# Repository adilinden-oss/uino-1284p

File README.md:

## \*uino-1284p 

\*uino-1284p is an Arduino compatible platform based on the Atmel ATmega1284P-AU microcontroller.

### Licensing

This work is licensed under a Creative Commons Attribution-ShareAlike 3.0 Unported License, CC BY-SA.

You are free to copy, distribute and transmit the work. You must attribute the work in the manner specified by the author or licensor (but not in any way that suggests that they endorse you or your use of the work). you alter, transform, or build upon this work, you may distribute the resulting work only under the same or similar license to this one.  

Please refer to [http://creativecommons.org/licenses/by-sa/3.0/] for the license.

### Credit

The \*uino-1284p is derived from previous work done by:

- The Arduino team <http://arduino.cc/>

### Details

The \*uino-1284p board utilizes the ATmega1284P microcontroller. The main goal of this project is to be able to access more memory, both FLASH and RAM, while keeping the Arduino UNO compatible board size and I/O assignments.

The ATmega1284P provides 128k of FLASH and 16k of RAM. It has 10 more I/O pins then the ATmega328P. The additional I/O pins are brought out to a 5x2 header in a non-standard Arduino position. The extra header pins are :

        L1/D16  o|o  L2/D17
           D18  o|o  D19
           D20  o|o  D21
           D22  o|o  D23
        D24/A6  o|o  D25/A7

The design features a dedicated ATmega8U2 for USB connectivity. The circuit has been taken from the Arduino UNO but the TQFP-32 package was chosen for easy solderability.

Power supply input for the board is selected via a jumper. Power supply options are USB bus powered or unregulated DC input. An onboard LDO regulator will accept an unregulated input voltage between 6.4V and 15V.

### Arduino

The board is supported in Arduino IDE 1.6.x via the core files available at: [adilinden-oss/uino-arduino](https://github.com/adilinden-oss/uino-arduino)

To install clone uino-arduino into the hardware folder inside your Sketchbook folder. The board will then automagically appear in the Boards menu.

### Pin Mapping

```
*uino     ATmega1284p                     Function
A0  D26   32 - PA5 (PCINT5/ADC5)
A1  D27   33 - PA4 (PCINT4/ADC4)
A2  D28   34 - PA3 (PCINT3/ADC3)
A3  D29   35 - PA2 (PCINT2/ADC2)
A4  D30   36 - PA1 (PCINT1/ADC1)
A5  D31   37 - PA0 (PCINT0/ADC0)

D0        9  - PD0 (PCINT24/RXD0/T3)      UART RX0
D1        10 - PD1 (PCINT25/TXD0)         UART TX0
D2        11 - PD2 (PCINT26/RXD1/INT0)    IRQ2, UART RX1
D3        12 - PD3 (PCINT27/TXD1/INT1)    IRQ3, UART TX1
D4        13 - PD4 (PCINT28/XCK1/OC1B)    PWM
D5        14 - PD5 (PCINT29/OC1A)         PWM
D6        15 - PD6 (PCINT30/OC2B/ICP)     PWM
D7        16 - PD7 (PCINT31/OC2A)         PWM

D8        42 - PB2 (PCINT10/INT2/AIN0)  
D9        43 - PB3 (PCINT11/OC0A/AIN1)    PWM
D10       44 - PB4 (PCINT12/OC0B/SS)      PWM, SPI SS
D11       1  - PB5 (PCINT13/ICP3/MOSI)    SPI MOSI
D12       2  - PB6 (PCINT14/OC3A/MISO)    PWM, SPI MISO
D13       3  - PB7 (PCINT15/OC3B/SCK)     PWM, SPI SCK, LED

SCL D14   19 - PC0 (PCINT16/SCL)          SCL
SDA D15   20 - PC1 (PCINT17/SDA)          SDA
L1  D16   21 - PC2 (PCINT18/TCK)          L1
L2  D17   22 - PC3 (PCINT19/TMS)          L2

D18       23 - PC4 (PCINT20/TDO)
D19       24 - PC5 (PCINT21/TDI)
D20       25 - PC6 (PCINT22/TOSC1)
D21       26 - PC7 (PCINT23/TOSC2)
D22       40 - PB0 (PCINT8/T0/XCK0)
D23       41 - PB1 (PCINT9/T1/CLK0)
A6  D24   30 - PA7 (PCINT7/ADC7)
A7  D25   31 - PA6 (PCINT6/ADC6)
```

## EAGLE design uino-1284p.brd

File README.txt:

*uino-1284p is an Arduino compatible platform based on the ATmega1284P-AU

Licensing
---------
This work is licensed under a Creative Commons Attribution-ShareAlike 3.0 
Unported License, CC BY-SA.

You are free to copy, distribute and transmit the work. You must attribute 
the work in the manner specified by the author or licensor (but not in any
way that suggests that they endorse you or your use of the work). you alter,
transform, or build upon this work, you may distribute the resulting work
only under the same or similar license to this one.  

Please refer to <http://creativecommons.org/licenses/by-sa/3.0/> for the
license.

Credit
------
The *uino-1284p is derived from previous work done by:
- The Arduino team <http://arduino.cc/>

Details
-------
The *uino-1284p board utilizes the ATmega1284P microcontroller. The main goal of
this project is to be able to access more memory, both FLASH and RAM, while
keeping the Arduino UNO compatible board size and I/O assignments.

The ATmega1284P provides 128k of FLASH and 16k of RAM. It has 10 more I/O pins
then the ATmega328P. The additional I/O pins are brought out to a 5x2 header
in a non-standard Arduino position.

The design features a dedicated ATmega8U2 for USB connectivity. The circuit
has been taken from the Arduino UNO but the TQFP-32 package was chosen for easy
solderability.

Power supply input for the board is selected via a jumper. Power supply options
are USB bus powered or unregulated DC input. An onboard LDO regulator will accept
an unregulated input voltage between 6.4V and 15V.

Arduino
-------
The board is supported in Arduino IDE 1.6.x via the core files available at:
https://github.com/adilinden/uino-arduino

To install clone uino-arduino into the hardware folder inside your Sketchbook
folder. The board will then automagically appear in the Boards menu.

Pin Mapping
-----------

Note that the pin mappings do not quite match the schematic diagram.  Header
J6 which is the 5x2 header provided for additional I/O has been renumbered.
The schematic diagram will have to be updated some time.  Since these are not
labelled on the board there are no other visible changes.

The new header pins are now:

		L1/D16  o|o  L2/D17
		   D18  o|o  D19
		   D20  o|o  D21
		   D22  o|o  D23
		D24/A6  o|o  D25/A7

*uino     ATmega1284p                     Function
A0  D26   32 - PA5 (PCINT5/ADC5)
A1  D27   33 - PA4 (PCINT4/ADC4)
A2  D28   34 - PA3 (PCINT3/ADC3)
A3  D29   35 - PA2 (PCINT2/ADC2)
A4  D30   36 - PA1 (PCINT1/ADC1)
A5  D31   37 - PA0 (PCINT0/ADC0)

D0        9  - PD0 (PCINT24/RXD0/T3)      UART RX0
D1        10 - PD1 (PCINT25/TXD0)         UART TX0
D2        11 - PD2 (PCINT26/RXD1/INT0)    IRQ2, UART RX1
D3        12 - PD3 (PCINT27/TXD1/INT1)    IRQ3, UART TX1
D4        13 - PD4 (PCINT28/XCK1/OC1B)    PWM
D5        14 - PD5 (PCINT29/OC1A)         PWM
D6        15 - PD6 (PCINT30/OC2B/ICP)     PWM
D7        16 - PD7 (PCINT31/OC2A)         PWM

D8        42 - PB2 (PCINT10/INT2/AIN0)  
D9        43 - PB3 (PCINT11/OC0A/AIN1)    PWM
D10       44 - PB4 (PCINT12/OC0B/SS)      PWM, SPI SS
D11       1  - PB5 (PCINT13/ICP3/MOSI)    SPI MOSI
D12       2  - PB6 (PCINT14/OC3A/MISO)    PWM, SPI MISO
D13       3  - PB7 (PCINT15/OC3B/SCK)     PWM, SPI SCK, LED

SCL D14   19 - PC0 (PCINT16/SCL)          SCL
SDA D15   20 - PC1 (PCINT17/SDA)          SDA
L1  D16   21 - PC2 (PCINT18/TCK)          L1
L2  D17   22 - PC3 (PCINT19/TMS)          L2

D18       23 - PC4 (PCINT20/TDO)
D19       24 - PC5 (PCINT21/TDI)
D20       25 - PC6 (PCINT22/TOSC1)
D21       26 - PC7 (PCINT23/TOSC2)
D22       40 - PB0 (PCINT8/T0/XCK0)
D23       41 - PB1 (PCINT9/T1/CLK0)
D24  A6   30 - PA7 (PCINT7/ADC7)
D25  A7   31 - PA6 (PCINT6/ADC6)

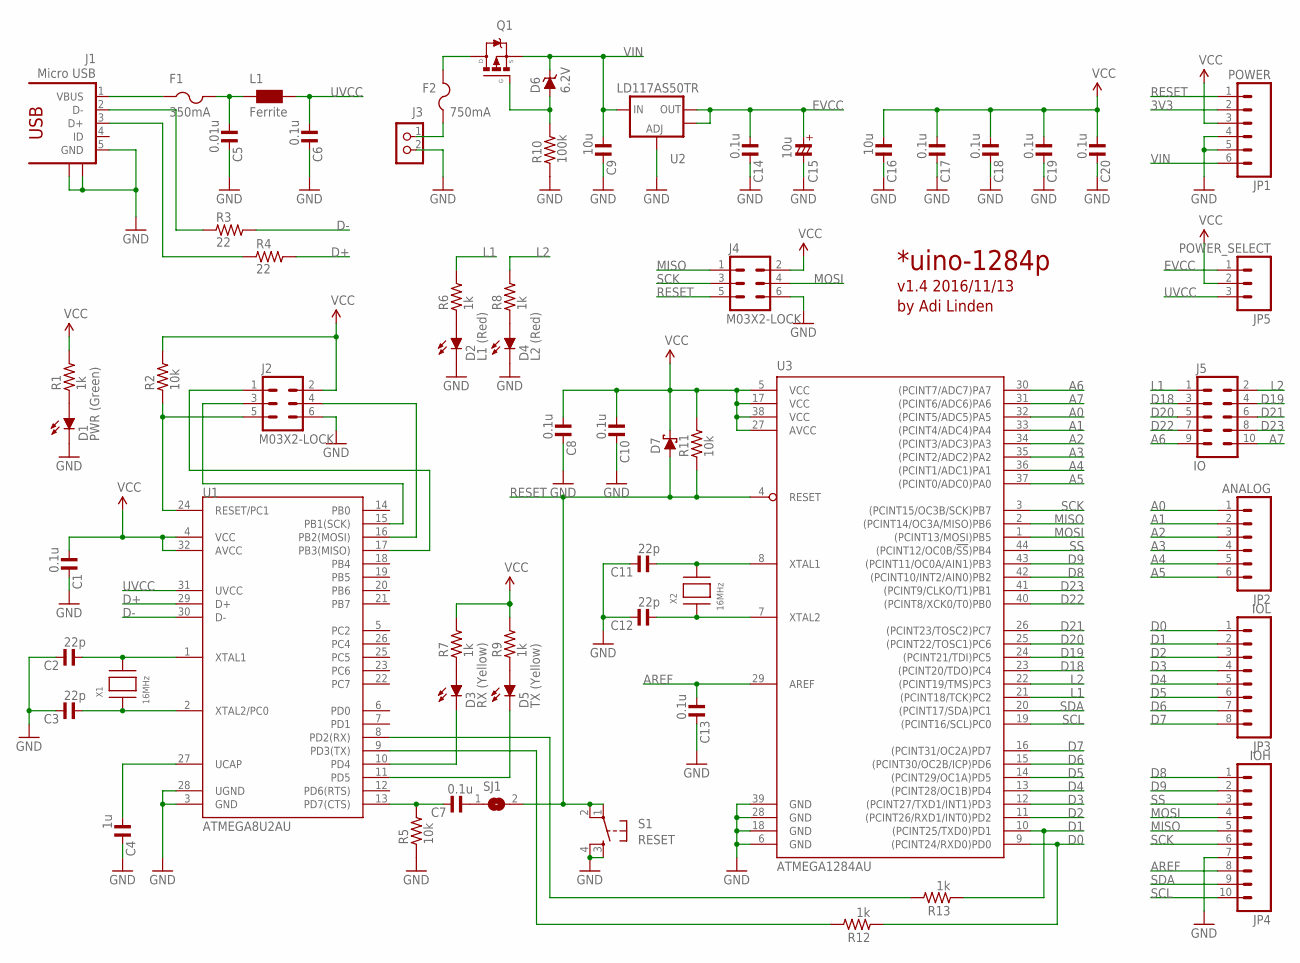
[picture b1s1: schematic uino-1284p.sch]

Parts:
C1, C6, C7, C8, C10, C13, C14, C17, C18, C19, C20: 0.1u; C0805MP
C2, C3, C11, C12: 22p; C0805MP
C4: 1u; C0805MP
C5: 0.01u; C0805MP
C9, C16: 10u; C0805MP
C15: 10u; C0805MP/T
D1: PWR (Green); CHIP-LED0805MP
D2: L1 (Red); CHIP-LED0805MP
D3: RX (Yellow); CHIP-LED0805MP
D4: L2 (Red); CHIP-LED0805MP
D5: TX (Yellow); CHIP-LED0805MP
D6: 6.2V; SOD323
D7: SCHOTTKY-DIODESOD323; SOD323
F1: 350mA; R0805
F2: 750mA; R0805
J1: Micro USB; ZX62D-AB-5P8
J2, J4: M03X2-LOCK; 2X03_LOCK
J3: CON_TERMINAL_BLOCK_02-5MM; TERMINAL_BLOCK_2P_5
J5: IO; 2X05
JP1: POWER; 1X06
JP2: ANALOG; 1X06
JP3: IOL; 1X08
JP4: IOH; 1X10
JP5: POWER_SELECT; 1X03
L1: Ferrite; 0805
Q1: MMBF0202PLT1; SOT23
R1, R6, R7, R8, R9, R12, R13: 1k; R0805MP
R2, R5, R11: 10k; R0805MP
R3, R4: 22; R0805MP
R10: 100k; R0805MP
S1: RESET; TACTILE_SWITCH_SMD
SJ1: SJ
U1: ATMEGA8U2AU; TQFP32-08
U2: LD117AS50TR; SOT223
U3: ATMEGA1284AU; TQFP44
X1, X2: 16MHz; NX5032

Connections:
3V3: JP1.2
A0: JP2.1, U3.32 ((PCINT5/ADC5)PA5)
A1: JP2.2, U3.33 ((PCINT4/ADC4)PA4)
A2: JP2.3, U3.34 ((PCINT3/ADC3)PA3)
A3: JP2.4, U3.35 ((PCINT2/ADC2)PA2)
A4: JP2.5, U3.36 ((PCINT1/ADC1)PA1)
A5: JP2.6, U3.37 ((PCINT0/ADC0)PA0)
A6: J5.9, U3.30 ((PCINT7/ADC7)PA7)
A7: J5.10, U3.31 ((PCINT6/ADC6)PA6)
AREF: C13.1, JP4.8, U3.29 (AREF)
D0: JP3.1, R12.1, U3.9 ((PCINT24/RXD0)PD0)
D1: JP3.2, R13.1, U3.10 ((PCINT25/TXD0)PD1)
D2: JP3.3, U3.11 ((PCINT26/RXD1/INT0)PD2)
D3: JP3.4, U3.12 ((PCINT27/TXD1/INT1)PD3)
D4: JP3.5, U3.13 ((PCINT28/OC1B)PD4)
D5: JP3.6, U3.14 ((PCINT29/OC1A)PD5)
D6: JP3.7, U3.15 ((PCINT30/OC2B/ICP)PD6)
D7: JP3.8, U3.16 ((PCINT31/OC2A)PD7)
D8: JP4.1, U3.42 ((PCINT10/INT2/AIN0)PB2)
D9: JP4.2, U3.43 ((PCINT11/OC0A/AIN1)PB3)
D18: J5.3, U3.23 ((PCINT20/TDO)PC4)
D19: J5.4, U3.24 ((PCINT21/TDI)PC5)
D20: J5.5, U3.25 ((PCINT22/TOSC1)PC6)
D21: J5.6, U3.26 ((PCINT23/TOSC2)PC7)
D22: J5.7, U3.40 ((PCINT8/XCK0/T0)PB0)
D23: J5.8, U3.41 ((PCINT9/CLKO/T1)PB1)
D+: R4.2, U1.29 (D+)
D-: R3.2, U1.30 (D-)
EVCC: C14.1, C15.+, JP5.1, U2.2 (OUT), U2.4 (OUT)
GND: C1.2, C2.2, C3.2, C4.2, C5.2, C6.2, C8.2, C9.2, C10.2, C11.2, C12.2, C13.2, C14.2, C15.-, C16.2, C17.2, C18.2, C19.2, C20.2, D1.C, D2.C, D4.C, J1.5 (GND), J1.S1, J1.S2, J2.6, J3.2, J4.6, JP1.4, JP1.5, JP4.7, R5.1, R10.1, S1.3, S1.4, U1.3 (GND), U1.28 (UGND), U2.1 (ADJ), U3.6 (GND), U3.18 (GND), U3.28 (GND), U3.39 (GND)
L1: J5.1, R6.2, U3.21 ((PCINT18/TCK)PC2)
L2: J5.2, R8.2, U3.22 ((PCINT19/TMS)PC3)
MISO: J4.1, JP4.5, U3.2 ((PCINT14/OC3A/MISO)PB6)
MOSI: J4.4, JP4.4, U3.1 ((PCINT13/MOSI)PB5)
unnamed: F2.2, Q1.3 (D)
unnamed: C5.1, F1.2, L1.1
unnamed: C7.1, SJ1.1
unnamed: J1.2 (D-), R3.1
unnamed: J1.3 (D+), R4.1
unnamed: R12.2, U1.9 (PD3(TX))
unnamed: R13.2, U1.8 (PD2(RX))
unnamed: C2.1, U1.1 (XTAL1), X1.P$2
unnamed: C3.1, U1.2 (XTAL2/PC0), X1.P$1
unnamed: C4.1, U1.27 (UCAP)
unnamed: D2.A, R6.1
unnamed: D4.A, R8.1
unnamed: J2.1, U1.17 (PB3(MISO))
unnamed: J2.3, U1.15 (PB1(SCK))
unnamed: J2.5, R2.1, U1.24 (RESET/PC1)
unnamed: J2.4, U1.16 (PB2(MOSI))
unnamed: F2.1, J3.1
unnamed: D6.A, Q1.1 (G), R10.2
unnamed: C11.1, U3.8 (XTAL1), X2.P$2
unnamed: C12.1, U3.7 (XTAL2), X2.P$1
unnamed: D3.A, R7.1
unnamed: D5.A, R9.1
unnamed: D3.C, U1.10 (PD4)
unnamed: D5.C, U1.11 (PD5)
unnamed: C7.2, R5.2, U1.13 (PD7(CTS))
unnamed: D1.A, R1.1
RESET: D7.A, J4.5, JP1.1, R11.1, S1.1, S1.2, SJ1.2, U3.4 (RESET)
SCK: J4.3, JP4.6, U3.3 ((PCINT15/OC3B/SCK)PB7)
SCL: JP4.10, U3.19 ((PCINT16/SCL)PC0)
SDA: JP4.9, U3.20 ((PCINT17/SDA)PC1)
SS: JP4.3, U3.44 ((PCINT12/OC0B/!SS!)PB4)
UVCC: C6.1, JP5.3, L1.2, U1.31 (UVCC)
VBUS: F1.1, J1.1 (VBUS)
VCC: C1.1, C8.1, C10.1, C16.1, C17.1, C18.1, C19.1, C20.1, D7.C, J2.2, J4.2, JP1.3, JP5.2, R1.2, R2.2, R7.2, R9.2, R11.2, U1.4 (VCC), U1.32 (AVCC), U3.5 (VCC), U3.17 (VCC), U3.27 (AVCC), U3.38 (VCC)
VIN: C9.1, D6.C, JP1.6, Q1.2 (S), U2.3 (IN)

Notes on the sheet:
*uino-1284p
v1.4 2016/11/13
by Adi Linden

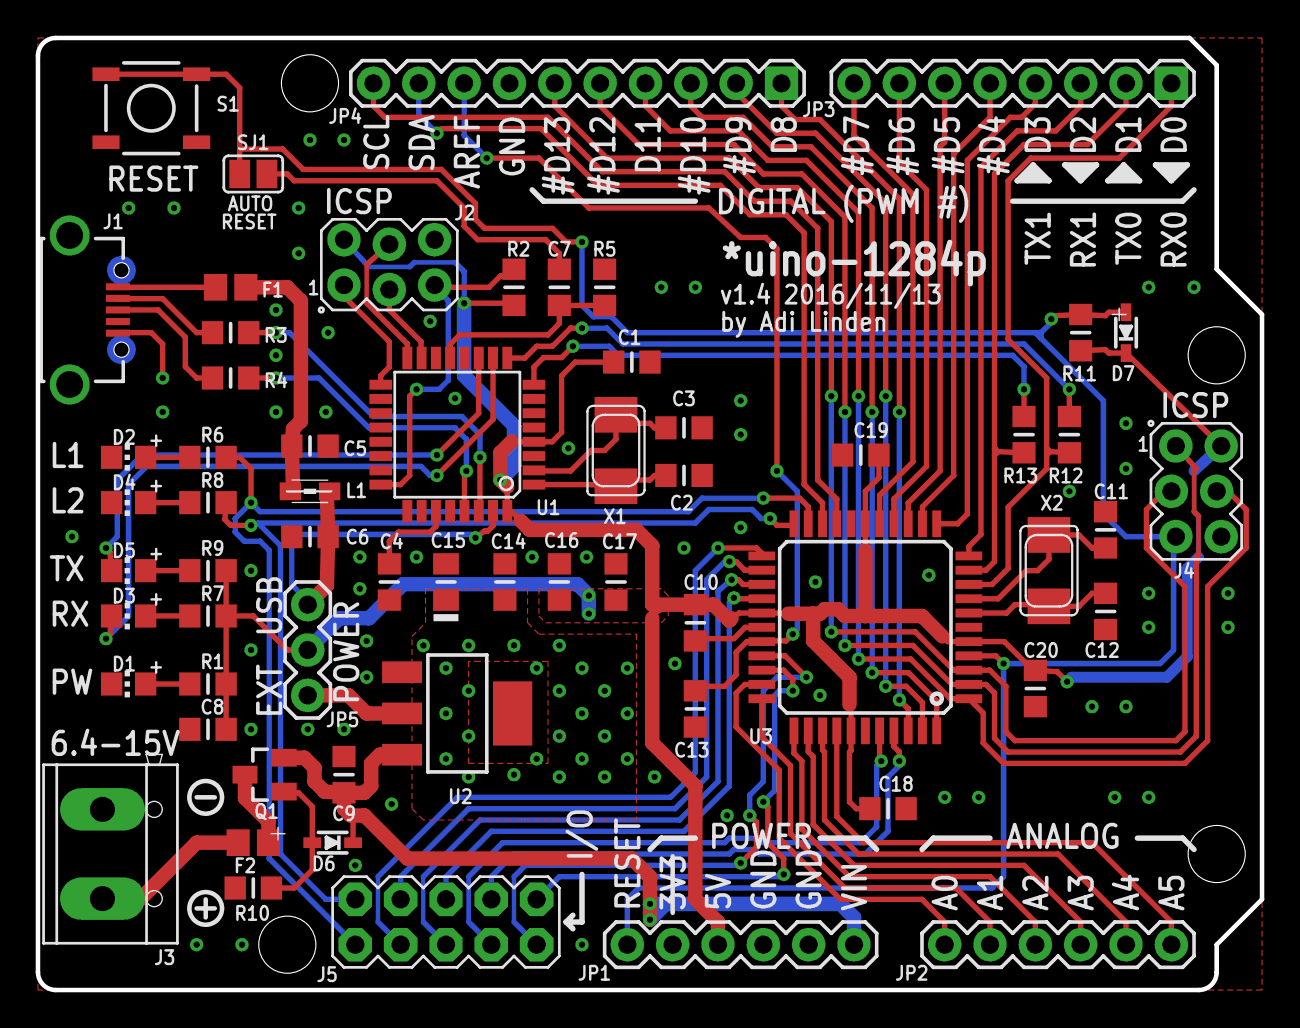
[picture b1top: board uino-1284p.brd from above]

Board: 2 copper layers, 68.6 x 53.3 mm, 61 parts (0 on the bottom side), 68 nets.

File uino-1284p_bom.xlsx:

Part | Quantity | Value | Manufacturer Part Number | DigiKey Part Number | Package | Description
C1, C6, C7, C8, C10, C13, C14, C17, C18, C19, C20 | 11 | 0.1u | CL21B104KBFNNNG | 1276-6468-1-ND | C0805 | 0.10µF ±10% 50V Ceramic Capacitor X7R 0805 (2012 Metric)
C2, C3, C11, C12 | 4 | 22p | CL21C220JBANNNC | 1276-1047-1-ND | C0805 | 22pF ±5% 50V Ceramic Capacitor C0G, NP0 0805 (2012 Metric)
C4 | 1 | 1u | CL21B105KOFNNNG | 1276-6471-1-ND | C0805 | 1µF ±10% 16V Ceramic Capacitor X7R 0805 (2012 Metric)
C5 | 1 | 0.01u | CL21B103KBANNNC | 1276-1015-1-ND | C0805 | 10000pF ±10% 50V Ceramic Capacitor X7R 0805 (2012 Metric)
C9, C16 | 2 | 10u | CL21A106KOQNNNG | 1276-6455-1-ND | C0805 | 10µF ±10% 16V Ceramic Capacitor X5R 0805 (2012 Metric)
C15 | 1 | 10u | F920J106MPA | 478-8115-1-ND | C0805 | 10µF ±20% Molded Tantalum Capacitors 6.3V 0805 (2012 Metric) 6 Ohm
D1 | 1 | 6.2V Zener | DZ2J062M0L | DZ2J062M0LCT-ND | SOD323 | Zener Diode 6.2V 200mW ±5% Surface Mount SMini2-F5-B
D2 | 1 | 1A Schottky | DB2J31700LCT-ND | DB2J31700L | SOD323 | Diode Schottky 30V 1A Surface Mount SMini2-F5-B
F1 | 1 | 350mA | 0ZCK0035FF2G | 507-1812-1-ND | R0805 | PTC Resettable Fuse 6V 350mA Ih Surface Mount 0805 (2012 Metric), Concave
F2 | 1 | 750mA | 0ZCK0075FF2E | 507-1814-1-ND | R0805 | PTC Resettable Fuse 6V 750mA Ih Surface Mount 0805 (2012 Metric), Concave
J1 | 1 | Micro USB | 475890001 | WM17143CT-ND | ZX62D-AB-5P8 | USB - micro AB Receptacle Connector 5 Position Surface Mount, Right Angle, Hori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
J2, J4 | 2 | Header 2x3 | M20-9980345 | 952-2120-ND | 2X03 | 6 Positions Header, Unshrouded, Breakaway Connector 0.100" (2.54mm) Through Hol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
J3 | 1 | Terminal | OSTTC022162 | ED2609-ND | 7.6x10.16mm | 2 Position Wire to Board Terminal Block Horizontal with Board 0.200" (5.08mm) T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
J5 | 1 | Header 2x5 | PPTC052LFBN-RC | S6105-ND | 2X05 | 10 Position Header Connector 0.100" (2.54mm) Through Hole Tin
JP1, JP2 | 2 | Header 1x6 | PPTC061LFBN-RC | S7004-ND | 1X06 | 6 Position Header Connector 0.100" (2.54mm) Through Hole Tin
JP3 | 1 | Header 1x8 | PPTC081LFBN-RC | S7006-ND | 1X08 | 8 Position Header Connector 0.100" (2.54mm) Through Hole Tin
JP4 | 1 | Header 1x10 | PPTC101LFBN-RC | S7008-ND | 1X10 | 10 Position Header Connector 0.100" (2.54mm) Through Hole Tin
JP5 | 1 | Header 1x3 | M20-9990345 | 952-2263-ND | 1X03 | Header 3
L1 | 1 | Ferrite | MI0805K400R-10 | 240-2389-1-ND | L0805 | FERRITE BEAD 40 OHM 0805 1LN
LED1 | 1 | PWR (Green) | LTST-S220KGKT | 160-1468-1-ND | CHIP-LED0805 | Green 568nm LED Indication - Discrete 2V 0805 (2012 Metric)
LED2, LED4 | 2 | L1 (Red) | LTST-S220KRKT | 160-1469-1-ND | CHIP-LED0805 | Red 631nm LED Indication - Discrete 2V 0805 (2012 Metric)
LED3, LED5 | 2 | RX (Yellow) | LTST-S220KSKT | 160-1470-1-ND | CHIP-LED0805 | Yellow 589nm LED Indication - Discrete 2V 0805 (2012 Metric)
Q1 | 1 | P-FET | IRLML2244TRPBF | IRLML2244TRPBFCT-ND | SOT23 | MOSFET P-CH 20V 4.3A SOT23
R1, R6, R7, R8, R9, R12, R13 | 7 | 1k | RC0805JR-071KL | 311-1.0KARCT-ND | R0805 | RES SMD 1K OHM 5% 1/8W 0805
R2, R5, R11 | 3 | 10k | RC0805JR-0710KL | 311-10KARCT-ND | R0805 | RES SMD 10K OHM 5% 1/8W 0805
R3, R4 | 2 | 22 | RC0805JR-0722RL | 311-22ARCT-ND | R0805 | RES SMD 22 OHM 5% 1/8W 0805
R10 | 1 | 100k | RC0805JR-07100KL | 311-100KARCT-ND | R0805 | RES SMD 100K OHM 5% 1/8W 0805
S1 | 1 | RESET | TL3305AF160QG | EG5350CT-ND | 4.50x4.50mm | Tactile Switch SPST-NO Top Actuated Surface Mount
U1 | 1 | ATMEGA8U2AU | ATMEGA8U2-AUR | ATMEGA8U2-AURCT-ND | TQFP32-08 | Atmel 8-bit Microcontroller with 8/16/32K Bystes of ISP Flash and USB Controlle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
U2 | 1 | LD1117S50 | AZ1117IH-5.0TRG1 | AZ1117IH-5.0TRG1DICT-ND | SOT223 | Voltage Regulator LM1117
U3 | 1 | ATMEGA1284AU | ATMEGA1284P-AUR | ATMEGA1284P-AURCT-ND | TQFP44 | 8-bit Microcontroller with 64K Bytes In-System Programmable Flash
X1, X2 | 2 | 16MHz | NX5032GA-16.000000MHZ-LN-CD-1 | 644-1037-1-ND | NX5032 | Low cost SMT crystals, no capacitors included

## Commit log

2011-12-29 Added .gitignore to prevent Eagle backup files from being tracked.
2011-12-30 Completed the board layout. Completed silk screen.
2011-12-30 Added several files.
    Added board, schematic and Gerber files for v0.2.
    Added PNG for v0.2.
2011-12-31 Updated to v0.3.
    - Added 5x2 header to make additional I/O available.
    - Replaced shottky diode on USB supply with jumper for input
    supply voltage selection.
2011-12-31 Added pin assignment for v0.3
2011-12-31 Fixed tabs
2011-12-31 More tab fixes
2016-03-03 Files submitted to Seeed FusionPCB for manufacturing.
2016-10-17 Updated pin mapping. Added reference to Arduino files.
2016-10-17 Corrected PCINT labelling on analog A0-A5.
2016-10-19 Changed net labels to match uino-arduino core board definitions.
2016-10-19 Updated README.md.
2016-10-19 Beautified title.
2016-10-31 Refactor to place eagle files into root.
2016-11-04 Unified device name text on board. Arranged name labels.
2016-11-04 Changed to micro USB. Moved USB ICSP header.
2016-11-04 Fixed LED names and placements.
2016-11-05 Made prefix for IC consistent.
2016-11-05 Moved VCC lines. Fixed more naming.
2016-11-05 Added BOM.
2016-11-05 Changed power input jack to screw terminal.
2016-11-05 Added eagle project file.
2016-11-05 Renamed power jack.
2016-11-05 Updated BOM.
2016-11-05 Changed power jack orientation.
2016-11-05 Added quantity column in BOM.
2016-11-07 Increased text sizes. Optimized polygon fills and routing.
2016-11-07 Fixed some labels.
2016-11-08 Board image with polygons filled.
2016-11-09 Replaced reverse polarity schottky with P-FET.
2016-11-09 Fixed values and numbering.
2016-11-09 Changed tantalum to 0805 and ceramic. Made use of extra space.
2016-11-09 Corrected X2 and J2 label.
2016-11-13 Added polygon to have voltage regulator without thermals for better heat sinking.
2016-11-14 Changed ISP header to offset style making use of permanent header optional (hopefully).
2016-11-14 Version 1.4.
2016-11-17 Created gerber for FusionPCB order.
2019-02-22 Fixed formatting and updated URL.

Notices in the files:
parts and their libraries:
rc-master-smd: Copyright (C) 2007-2008, Bob Starr
